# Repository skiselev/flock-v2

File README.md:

# Flock - Version 2.0
Floppy Disk Controller and Real Time Clock for RCBus systems

## Table of Content
* [Overview](#overview)
  * [Specifications](#specifications)
* [Assembly Instructions](#assembly-instructions)
* [Hardware Documentation](#hardware-documentation)
  * [Schematic and PCB Layout](#schematic-and-pcb-layout)
  * [Input/Output Ports](#inputoutput-ports)
  * [Connectors](#connectors)
  * [Bill of Materials](#bill-of-materials)
* [Release Notes](#release-notes)
  * [Changes](#changes)
  * [Known Issues](#known-issues)
* [Red Tape](#red-tape)
  * [Licensing](#licensing)
  * [Trademarks](#trademarks)

## Overview
Flock is an RCBus floppy disk controller (FDC) and real time clock (RTC) module. It designed to work with RomWBW firmware, supporting CP/M, ZSDOS, and various applications under these OSes.

### Specifications
* Floppy Disk Controller: Western Digital* WD37C65 or compatible
  * NEC uPD765 compatible with an integrated data separator, floppy interface drivers, and buffers
* Supported floppy disk formats:
  * 3.5", 720 KB
  * 3.5", 1.44 MB
  * 5.25", 360 KB diskettes in 360 MB drive
  * 5.25", 1.2 MB
  * 5.25", 360 KB diskettes in 1.2 MB drive (not supported by RomWBW, requires Y3, C10, and C11 to be installed)
* Supports two floppy drives, using IBM PC-like cable with twisted Disk Select / Motor Enable wires between two drives
* Real Time Clock: Maxim Integrated DS1302
* Bus: RCBus, RC2014* compatible

## Assembly Instructions

Please refer to [Assembly Instructions](Assembly_Instructions.md) document

## Hardware Documentation

### Schematic and PCB Layout

[Schematic - Version 2.0](KiCad/Z80-FDC-V2-Schematic-2.0.pdf)

[PCB Layout - Version 2.0](KiCad/Z80-FDC-V2-Board-2.0.pdf)

### Input/Output Ports

Flock uses the following I/O ports:

#### 0x48 - FDC CCR/DIR

Write: Floppy disk controller control configuration register (CCR)
Read: Floppy disk controller digital input register (DIR)

#### 0x50 - FDC MSR

Read: Floppy disk controller master status register (MSR)

#### 0x51 - FDC Data Register

Read/Write: Data from/to floppy disk controller

#### 0x58 - FDC DOR / TC

Write: Floppy disk controller digital output register (DOR)
Read: Toggle floppy disk controller transfer complete (TC) line

#### 0x0C or 0xC0 - RTC

Read/Write: Access real time clock (RTC)
The RTC address is configured using JP1 jumper

### Jumpers and Connectors

#### JP1 - RTC I/O address select

Position       | Description
-------------- | -----------------
open (default) | RTC address: 0xC0
closed         | RTC address: 0x0C

* Use 0xC0 address for Z80-based systems and 0x0C address for Z180-based systems

#### JP2 - Enable RTC

Position       | Description
-------------- | -----------------
1-2 (default)  | RTC enabled
2-3            | RTC disabled

* JP2 is a solder jumper, located on the back of the board
* By default positions 1-2 are connected with a PCB trace
* If the system already has an RTC or the RTC functionality is not needed:
  * Cut the PCB trace between positions 1-2
  * Connect positions 2-3 with a solder bridge

#### JP3 - Enable 300 Kbps transfer rate support

Position       | Description
-------------- | -----------------
1-2 (default)  | 300 Kbps disabled
2-3            | 300 Kbps enabled

* JP3 is a solder jumper, located on the back of the board
* By default positions 1-2 are connected with a PCB trace
* If 300 Kbps is desired:
  * Cut the PCB trace between positions 1-2
  * Connect positions 2-3 with a solder bridge
  * Install Y3, C10, and C11

#### J1 - Floppy
Connect to floppy drive interface connector.

Pin   | Signal Name | Description   | Pin   | Signal Name | Description
----- | ----------- | --------------| ----- | ----------- | -----------
J1-1  | GND         | Ground        | J1-2  | /DENSEL     | Density Select: 1 = Low density; 0 = High density
J1-3  | N/C         | Not connected | J1-4  | N/C         | Not connected
J1-5  | GND         | Ground        | J1-6  | N/C         | Not connected
J1-7  | GND         | Ground        | J1-8  | /INDEX      | Index hole: 0 = At the index hole
J1-9  | N/C         | Not connected | J1-10 | /MEA        | Motor Enable - Drive A
J1-11 | GND         | Ground        | J1-12 | /DSB        | Drive Select - Drive B
J1-13 | GND         | Ground        | J1-14 | /DSA        | Drive Select - Drive A
J1-15 | GND         | Ground        | J1-16 | /MEB        | Motor Enable - Drive B
J1-17 | N/C         | Not connected | J1-18 | /DIR        | Direction Select
J1-19 | GND         | Ground        | J1-20 | /STEP       | Head Step
J1-21 | GND         | Ground        | J1-22 | /WDATA      | Write Data
J1-23 | GND         | Ground        | J1-24 | /WE         | Write Enable: 0 = Write Enabled
J1-25 | GND         | Ground        | J1-26 | /TRK0       | Track 00: 0 = At the track 0
J1-27 | N/C         | Not connected | J1-28 | /WP         | Write Protect: 0 = Floppy disk is write protected
J1-29 | GND         | Ground        | J1-30 | /RDATA      | Read Data 
J1-31 | GND         | Ground        | J1-32 | /HDSEL      | Head Select / Side Select: 1 = Side 0; 0 = Side 1
J1-33 | N/C         | Not connected | J1-34 | /DC         | Disk changed: 1 = Disk changed; 0 = Ready

#### J2 - Floppy 5V
Connect to floppy 5V power supply connector.

**Important: J2 is an unfused 5V power supply for a single 3.5" floppy disk drive. Avoid overloading and short-circuiting**

Pin | Signal Name | Description
--- | ----------- | -----------
1   | 5V          | Positive terminal - +5V
2   | GND         | Negative terminal - ground

#### J3 - RCBus
Pin   | Signal Name | Description                             | Pin   | Signal Name | Description
----- | ----------- | --------------------------------------- | ----- | ----------- | -----------
J3-1  | A15         | Address A15; Input; Not connected       | J3-41 | p41         | Reserved; Not connected
J3-2  | A14         | Address A14; Input; Not connected       | J3-42 | /BAI        | Bus Acknowledge In; Not connected
J3-3  | A13         | Address A13; Input; Not connected       | J3-43 | /BAO        | Bus Acknowledge Out; Not connected
J3-4  | A12         | Address A12; Input; Not connected       | J3-44 | p44         | Reserved; Not connected
J3-5  | A11         | Address A11; Input; Not connected       | J3-45 | p45         | Reserved; Not connected
J3-6  | A10         | Address A10; Input; Not connected       | J3-46 | p46         | Reserved; Not connected
J3-7  | A9          | Address A9; Input; Not connected        | J3-47 | p47         | Reserved; Not connected
J3-8  | A8          | Address A8; Input; Not connected        | J3-48 | p48         | Reserved; Not connected
J3-9  | A7          | Address A7; Input                       | J3-49 | A23         | Address A23; Input; Not connected
J3-10 | A6          | Address A6; Input                       | J3-50 | A22         | Address A22; Input; Not connected
J3-11 | A5          | Address A5; Input                       | J3-51 | A21         | Address A21; Input; Not connected
J3-12 | A4          | Address A4; Input                       | J3-52 | A20         | Address A20; Input; Not connected
J3-13 | A3          | Address A3; Input                       | J3-53 | A19         | Address A19; Input; Not connected
J3-14 | A2          | Address A2; Input                       | J3-54 | A18         | Address A18; Input; Not connected
J3-15 | A1          | Address A1; Input                       | J3-55 | A17         | Address A17; Input; Not connected
J3-16 | A0          | Address A0; Input                       | J3-56 | A16         | Address A16; Input; Not connected
J3-17 | GND         | Ground                                  | J3-57 | GND         | Ground
J3-18 | VCC         | Power Supply - +5V                      | J3-58 | VCC         | Power Supply - +5V
J3-19 | /M1         | Machine Cycle One; Input                | J3-59 | /RFSH       | DRAM refresh; Input; Not connected
J3-20 | /RESET      | Reset; Input                            | J3-60 | PAGE        | Page ROM/RAM input; Not connected
J3-21 | CLK1        | CPU Clock; Input; Not connected         | J3-61 | CLK2        | UART Clock (programmable); Input; Not connected
J3-22 | /INT        | Interrupt; Output; Not connected        | J3-62 | /BUSACK     | DMA Bus Acknowledge; Input; Not connected
J3-23 | /MREQ       | Memory Request; Input; Not connected    | J3-63 | /HALT       | Halt; Input; Not connected
J3-24 | /WR         | Write Request; Input                    | J3-64 | /BUSREQ     | DMA Bus Request; Output; Not connected
J3-25 | /RD         | Read Request; Input                     | J3-65 | /WAIT       | Wait; Output; Not connected
J3-26 | /IORQ       | Input/Output Request; Input             | J3-66 | /NMI        | Non-maskable Interrupt; Output; Not connected
J3-27 | D0          | Data D0; Input/Output                   | J3-67 | D8          | Data D8; Input/Output; Not connected
J3-28 | D1          | Data D1; Input/Output                   | J3-68 | D9          | Data D9; Input/Output; Not connected
J3-29 | D2          | Data D2; Input/Output                   | J3-69 | D10         | Data D10; Input/Output; Not connected
J3-30 | D3          | Data D3; Input/Output                   | J3-70 | D11         | Data D11; Input/Output; Not connected
J3-31 | D4          | Data D4; Input/Output                   | J3-71 | D12         | Data D12; Input/Output; Not connected
J3-32 | D5          | Data D5; Input/Output                   | J3-72 | D13         | Data D13; Input/Output; Not connected
J3-33 | D6          | Data D6; Input/Output                   | J3-73 | D14         | Data D14; Input/Output; Not connected
J3-34 | D7          | Data D7; Input/Output                   | J3-74 | D15         | Data D15; Input/Output; Not connected
J3-35 | TX          | Channel 1, Transmit Data; Not Connected | J3-75 | TX2         | Channel 2, Transmit Data; Not Connected
J3-36 | RX          | Channel 1, Receive Data; Not Connected  | J3-76 | RX2         | Channel 2, Receive Data; Not Connected
J3-37 | /IRQ1       | Interrupt Request 1; Not connected      | J3-77 | /IRQ2       | Interrupt Request 2; Not connected
J3-38 | IEI         | Interrupt Enable In; Not connected      | J3-78 | p78         | Reserved; Not connected
J3-39 | IEO         | Interrupt Enable Out; Not connected     | J3-79 | p79         | Reserved; Not connected
J3-40 | USER4       | User Pin 4; Not connected               | J3-80 | USER8       | User Pin 8; Not connected

### Bill of Materials

#### Version 2.0

[Flock V2 project on Mouser.com](https://www.mouser.com/ProjectManager/ProjectDetail.aspx?AccessID=57797d9ea4) - View and order all components except of the FDC and the PCB.

[Flock project on OSH Park](https://oshpark.com/shared_projects/vQHiVNa8) - View and order the PCB.

Flock project on Tindie: [Complete kit](https://www.tindie.com/products/weird/flock-v2-rcbus-module-kit/); [Flock PCB, FDC, RTC, and SPLD](https://www.tindie.com/products/weird/flock-v2-rcbus-module-pcb-fdc-rtc-and-spld/).

Component type     | Reference | Description                                 | Quantity | Possible sources and notes 
------------------ | --------- | ------------------------------------------- | -------- | --------------------------
PCB                |           | Flock PCB - Version 2.0                     | 1        | Buy from my Tindie store: [Complete kit](https://www.tindie.com/products/weird/flock-v2-rcbus-module-kit/); [Flock PCB, FDC, RTC, and SPLD](https://www.tindie.com/products/weird/flock-v2-rcbus-module-pcb-fdc-rtc-and-spld/)., or order from a PCB manufacturer of your choice using provided Gerber or KiCad files
Integrated Circuit | U1        | WD37C65BJM - FDC, CMOS, 44 pin PLCC         | 1        | eBay. Alternative: ST AIC37C65CL
Integrated Circuit | U2        | DS1302+ - RTC, 8 pin DIP                    | 1        | Mouser [700-DS1302](https://www.mouser.com/ProductDetail/700-DS1302)
Integrated Circuit | U3        | ATF16V8B-15PU - Simple Programmable Logic Device, 20 pin DIP | 1 | Mouser [556-AF16V8B15PU](https://www.mouser.com/ProductDetail/556-AF16V8B15PU)
Integrated Circuit | U4        | 74AHCT174 - Hex D-type flip-flop with reset, 16 pin DIP | 1 | Mouser [595-SN74AHCT174N](https://www.mouser.com/ProductDetail/595-SN74AHCT174N)
Integrated Circuit | U5        | 74HCT125 - Quadruple bus buffer gates with 3-state outputs, 14 pin DIP | 1 | Mouser [595-SN74HCT125NE4](https://www.mouser.com/ProductDetail/595-SN74HCT125NE4)
Quartz Crystal     | Y1        | 16 MHz, series                              | 1        | Mouser [774-ATS160-E](https://www.mouser.com/ProductDetail/774-ATS160-E)
Quartz Crystal     | Y2        | 32768 Hz, 6 pF                              | 1        | Mouser [815-AB26T32768KHZ6B](https://www.mouser.com/ProductDetail/815-AB26T32768KHZ6B)
Quartz Crystal     | Y3        | 9.6 MHz, series                             | 1        | Optional; Install for 300 Kbps transfer rate support
Connector          | J1        | 2x17 pin header, shrouded, 2.54 mm pitch, right angle | 1 | Mouser [517-30334-5002](https://www.mouser.com/ProductDetail/517-30334-5002)
Connector          | J2        | 2 pin header with friction lock, right angle | 1       | Mouser [571-2-644488-2](https://www.mouser.com/ProductDetail/571-2-644488-2)
Pin Header         | J3        | 2x40 pin header, 2.54 mm pitch, right angle | 1        | Mouser [517-5121TG](https://www.mouser.com/ProductDetail/517-5121TG)
Pin Header         | JP1       | 2 pin header, 2.54 mm pitch                 | 1        | Mouser [649-68002-102HLF](https://www.mouser.com/ProductDetail/649-68002-102HLF)
Jumper             | JP1       | Shunt, 2 pin 2.54 mm pitch                  | 1        | Mouser [806-SX1100-B](https://www.mouser.com/ProductDetail/806-SX1100-B)
Battery Holder     | BT1       | CR2032 battery holder                       | 1        | Mouser [122-2620-GR](https://www.mouser.com/ProductDetail/122-2620-GR) or [122-2420-GR](https://www.mouser.com/ProductDetail/122-2420-GR). Install either BT1 or C7
Battery            | BT1       | CR2032 battery                              | 1        | Mouser [81-CR2032](https://www.mouser.com/ProductDetail/81-CR2032), [658-CR2032](https://www.mouser.com/ProductDetail/658-CR2032), or [614-CR2032-200](https://www.mouser.com/ProductDetail/614-CR2032-200). Install either BT1 or C7
Capacitor          | C1 - C5   | 0.1 uF, 50V, MLCC, 5 mm pitch               | 5        | Mouser [810-FG28X7R1H104KNT6](https://www.mouser.com/ProductDetail/810-FG28X7R1H104KNT6)
Capacitor          | C6        | 10 uF, 47V, Organic Polymer, 6.3 mm diameter, 2.5 mm pitch | 1 | Mouser [80-A759EA106M1JAAE60](https://www.mouser.com/ProductDetail/80-A759EA106M1JAAE60). Note: PCB silkscreen specifies 47uF capacitor. 10uF - 47uF capacitor with voltage rating 10V or more can be used
Capacitor          | C7        | 0.22 F, 5.5V, Supercapacitor, 13.5 mm diameter, 5 mm pitch | 1 | Mouser [555-DBN-5R5D334T](https://www.mouser.com/ProductDetail/555-DBN-5R5D334T). Install either BT1 or C7
Capacitor          | C8        | 47 pF, 50V, MLCC, 5 mm pitch                | 1        | Mouser [810-FG28C0G2A470JNT0](https://www.mouser.com/ProductDetail/810-FG28C0G2A470JNT0)
Capacitor          | C9        | 15 pF, 50V, MLCC, 5 mm pitch                | 1        | Mouser [810-FG28C0G2A150JNT0](https://www.mouser.com/ProductDetail/810-FG28C0G2A150JNT0)
Capacitor          | C10       | 68 pF, 50V, MLCC, 5 mm pitch                | 1        | Optional; Install for 300 Kbps transfer rate support
Capacitor          | C11       | 56 pF, 50V, MLCC, 5 mm pitch                | 1        | Optional; Install for 300 Kbps transfer rate support
Resistor Array     | RN1       | 1 kohm, bussed, 6 pin SIP                   | 1        | Mouser [652-4606X-1LF-1K](https://www.mouser.com/ProductDetail/652-4606X-1LF-1K)
Resistor           | R1 - R3   | 10 kohm, 0.25 W, 1% tolerance, axial        | 3        | Mouser [603-MFR-25FRF5210K](https://www.mouser.com/ProductDetail/603-MFR-25FRF5210K)
IC Socket          | U1        | 44 pin PLCC, through hole                   | 1        | Mouser [649-54020-44030LF](https://www.mouser.com/ProductDetail/649-54020-44030LF), [517-8444-11B1-RK-TP](https://www.mouser.com/ProductDetail/517-8444-11B1-RK-TP)
IC Socket          | U2        | 8 pin DIP                                   | 1        | Mouser [649-DILB8P223TLF](https://www.mouser.com/ProductDetail/649-DILB8P223TLF)
IC Socket          | U3        | 20 pin DIP                                  | 1        | Mouser [649-DILB20P-223TLF](https://www.mouser.com/ProductDetail/649-DILB20P-223TLF)
IC Socket          | U4        | 16 pin DIP                                  | 1        | Mouser [649-DILB16P-223TLF](https://www.mouser.com/ProductDetail/649-DILB16P-223TLF)
IC Socket          | U5        | 14 pin DIP                                  | 1        | Mouser [649-DILB14P-223TLF](https://www.mouser.com/ProductDetail/649-DILB14P-223TLF)
Connector          | J2        | 2 pin connector                             | 1        | Mouser [571-3-643813-2](https://www.mouser.com/ProductDetail/571-3-643813-2)
Connector          | J2        | Floppy disk power connector housing         | 1        | Mouser [571-1718224](https://www.mouser.com/ProductDetail/571-1718224)
Connector          | J2        | Floppy disk power connector contacts        | 2        | Mouser [571-170262-2-LP](https://www.mouser.com/ProductDetail/571-170262-2-LP), [571-1702622-CT](https://www.mouser.com/ProductDetail/571-1702622-CT) (strip of 100 contacts)

## Release Notes

### Changes

* Version 2.0
  * Update form factor from RC2014* compatible to RCBus
  * Add an option to use CR2032 battery instead of a super capacitor for the RTC
  * Use right angle connector for the floppy interface
  * Use ATF16V8B SPLD for address decode
  * Add JP1 jumper for selecting RTC I/O address. Either 0xC0 or 0x0C can be used
  * Add JP2 jumper for disabling the RTC.
  * Add an option to support 300 Kbps transfer speed
  * Add a header for GPIO signals
* Version 1.0
  * Initial version

### Known Issues

* Version 1.0
  * No known issues

### Wishlist
* None so far

## Red Tape

### Licensing

Flock is an open source hardware project certified by [Open Source Hardware Association](https://www.oshwa.org/), certification UID is [US002115](https://certification.oshwa.org/us002115.html). The hardware design itself, including schematic and PCB layout design files are licensed under the strongly-reciprocal variant of [CERN Open Hardware Licence version 2](license-cern_ohl_s_v2.txt). The CPLD VHDL code is licensed under [GNU General Public License v3](license-gpl-3.0.txt). Documentation, including this file, is licensed under the [Creative Commons Attribution-ShareAlike 4.0 International License](license-cc-by-sa-4.0.txt).

### Trademarks

* "RC2014" is a registered trademark of RFC2795 Ltd.
* Other names and brands may be claimed as the property of others.

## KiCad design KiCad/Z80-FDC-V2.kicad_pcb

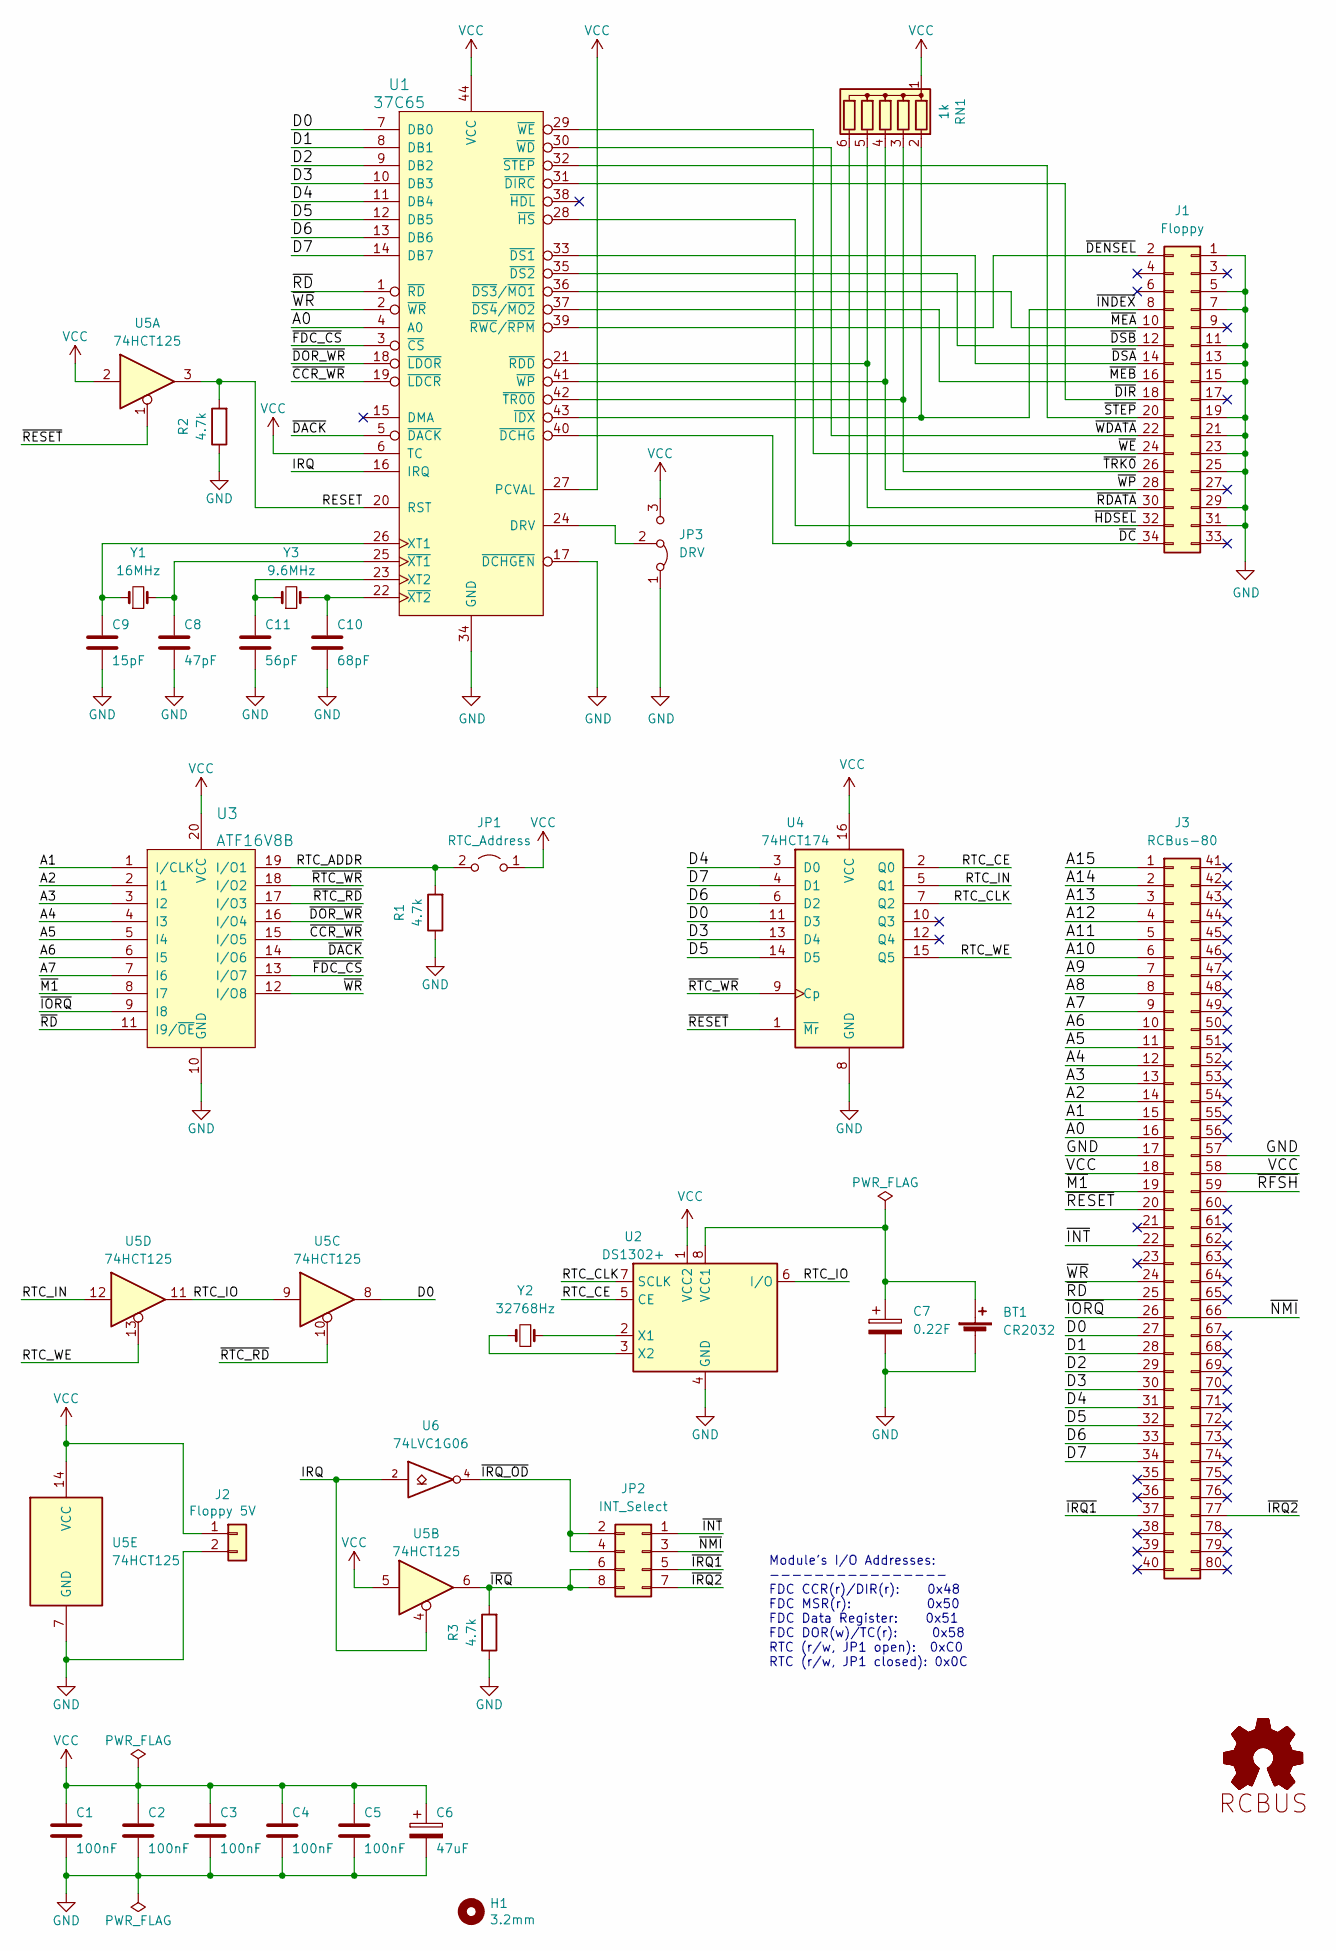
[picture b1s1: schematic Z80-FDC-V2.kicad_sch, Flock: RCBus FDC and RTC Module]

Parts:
BT1: CR2032; Battery_Holder_CR2032_Universal
C1, C2, C3, C4, C5: 100nF; Cap_Cer_508
C6: 47uF; Cap_Elec_Radial_6.3mm
C7: 0.22F; Cap_Super_Radial_13.5mm
C8: 47pF; Cap_Cer_508
C9: 15pF; Cap_Cer_508
C10: 68pF; Cap_Cer_508
C11: 56pF; Cap_Cer_508
H1: 3.2mm; MountingHole_3.2mm_M3_DIN965
J1: Floppy; Conn_Pin_Header_17x2_2.54mm_Shrouded_RA
J2: Floppy 5V; Conn_TE_2-644488-2_2P_2.54mm
J3: RCBus-80; Conn_Pin_Header_40x2_2.54mm_Right_Angle_RCBus80
JP1: RTC_Address; Conn_Pin_Header_2x1_2.54mm_NoKey
JP2: INT_Select; Conn_Pin_Header_4x2_2.54mm
JP3: DRV; Conn_Pin_Header_3x1_2.54mm
LOGO1, LOGO2: Logo_Open_Hardware_Small; OSHW-Logo_5.7x6mm_SilkScreen
LOGO3: RCBUS_Logo
R1, R2, R3: 4.7k; Res_762
RN1: 1k; Conn_SIL6
U1: 37C65; IC_PLCC44_TH
U2: DS1302+; IC_DIP8_300
U3: ATF16V8B; IC_DIP20_300
U4: 74HCT174; IC_DIP16_300
U5: 74HCT125; IC_DIP14_300
U6: 74LVC1G06; SOT-23-5_HandSoldering
Y1: 16MHz; Crystal_HC-49U_Vert
Y2: 32768Hz; Crystal_32K_Horiz
Y3: 9.6MHz; Crystal_HC-49U_Vert

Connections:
/A0: J3.16, U1.4 (A0)
/A1: J3.15, U3.1 (I/CLK)
/A2: J3.14, U3.2 (I1)
/A3: J3.13, U3.3 (I2)
/A4: J3.12, U3.4 (I3)
/A5: J3.11, U3.5 (I4)
/A6: J3.10, U3.6 (I5)
/A7: J3.9, U3.7 (I6)
/A8: J3.8
/A9: J3.7
/A10: J3.6
/A11: J3.5
/A12: J3.4
/A13: J3.3
/A14: J3.2
/A15: J3.1
/D0: J3.27, U1.7 (DB0), U4.11 (D3), U5.8
/D1: J3.28, U1.8 (DB1)
/D2: J3.29, U1.9 (DB2)
/D3: J3.30, U1.10 (DB3), U4.13 (D4)
/D4: J3.31, U1.11 (DB4), U4.3 (D0)
/D5: J3.32, U1.12 (DB5), U4.14 (D5)
/D6: J3.33, U1.13 (DB6), U4.6 (D2)
/D7: J3.34, U1.14 (DB7), U4.4 (D1)
/IRQ: U1.16 (IRQ), U5.4, U6.2
/RESET: R2.2, U1.20 (RST), U5.3
/RTC_ADDR: JP1.2 (B), R1.2, U3.19 (I/O1)
/RTC_CE: U2.5 (CE), U4.2 (Q0)
/RTC_CLK: U2.7 (SCLK), U4.7 (Q2)
/RTC_IN: U4.5 (Q1), U5.12
/RTC_IO: U2.6 (I/O), U5.9, U5.11
/RTC_WE: U4.15 (Q5), U5.13
/~CCR_WR: U1.19 (~LDCR), U3.15 (I/O5)
/~DACK: U1.5 (~DACK), U3.14 (I/O6)
/~DC: J1.34, RN1.6 (R5), U1.40 (~DCHG)
/~DENSEL: J1.2, U1.39 (~RWC/~RPM)
/~DIR: J1.18, U1.31 (~DIRC)
/~DOR_WR: U1.18 (~LDOR), U3.16 (I/O4)
/~DSA: J1.14, U1.33 (~DS1)
/~DSB: J1.12, U1.35 (~DS2)
/~FDC_CS: U1.3 (~CS), U3.13 (I/O7)
/~HDSEL: J1.32, U1.28 (~HS)
/~INDEX: J1.8, RN1.2 (R1), U1.43 (~IDX)
/~INT: J3.22, JP2.1
/~IORQ: J3.26, U3.9 (I8)
/~IRQ1: J3.37, JP2.5
/~IRQ2: J3.77, JP2.7
/~IRQ_OD: JP2.2, JP2.4, U6.4
/~IRQ: JP2.6, JP2.8, R3.2, U5.6
/~M1: J3.19, U3.8 (I7)
/~MEA: J1.10, U1.36 (~DS3/~MO1)
/~MEB: J1.16, U1.37 (~DS4/~MO2)
/~NMI: J3.66, JP2.3
/~RDATA: J1.30, RN1.5 (R4), U1.21 (~RDD)
/~RD: J3.25, U1.1 (~RD), U3.11 (I9/~OE)
/~RESET: J3.20, U4.1 (~Mr), U5.1
/~RFSH: J3.59
/~RTC_RD: U3.17 (I/O3), U5.10
/~RTC_WR: U3.18 (I/O2), U4.9 (Cp)
/~STEP: J1.20, U1.32 (~STEP)
/~TRK0: J1.26, RN1.3 (R2), U1.42 (~TR00)
/~WDATA: J1.22, U1.30 (~WD)
/~WE: J1.24, U1.29 (~WE)
/~WP: J1.28, RN1.4 (R3), U1.41 (~WP)
/~WR: J3.24, U1.2 (~WR), U3.12 (I/O8)
GND: BT1.2 (-), C1.2, C2.2, C3.1, C4.2, C5.2, C6.2, C7.2, C8.2, C9.2, C10.2, C11.2, J1.1, J1.5, J1.7, J1.11, J1.13, J1.15, J1.19, J1.21, J1.23, J1.25, J1.29, J1.31, J2.2, J3.17, J3.57, JP3.1 (A), R1.1, R2.1, R3.1, U1.17 (~DCHGEN), U1.34 (GND), U2.4 (GND), U3.10 (GND), U4.8 (GND), U5.7 (GND), U6.3 (GND)
unnamed: BT1.1 (+), C7.1, U2.8 (VCC1)
unnamed: C10.1, U1.22 (~XT2), Y3.2
unnamed: C11.1, U1.23 (XT2), Y3.1
unnamed: JP3.2 (C), U1.24 (DRV)
unnamed: C8.1, U1.25 (~XT1), Y1.2
unnamed: C9.1, U1.26 (XT1), Y1.1
unnamed: U2.2 (X1), Y2.1
unnamed: U2.3 (X2), Y2.2
VCC: C1.1, C2.1, C3.2, C4.1, C5.1, C6.1, J2.1, J3.18, J3.58, JP1.1 (A), JP3.3 (B), RN1.1 (common), U1.6 (TC), U1.27 (PCVAL), U1.44 (VCC), U2.1 (VCC2), U3.20 (VCC), U4.16 (VCC), U5.2, U5.5, U5.14 (VCC), U6.5 (VCC)

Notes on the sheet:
Module's I/O Addresses: ---------------- FDC CCR(r)/DIR(r): 0x48 FDC MSR(r): 0x50 FDC Data Register: 0x51 FDC DOR(w)/TC(r): 0x58 RTC (r/w, JP1 open): 0xC0 RTC (r/w, JP1 closed): 0x0C

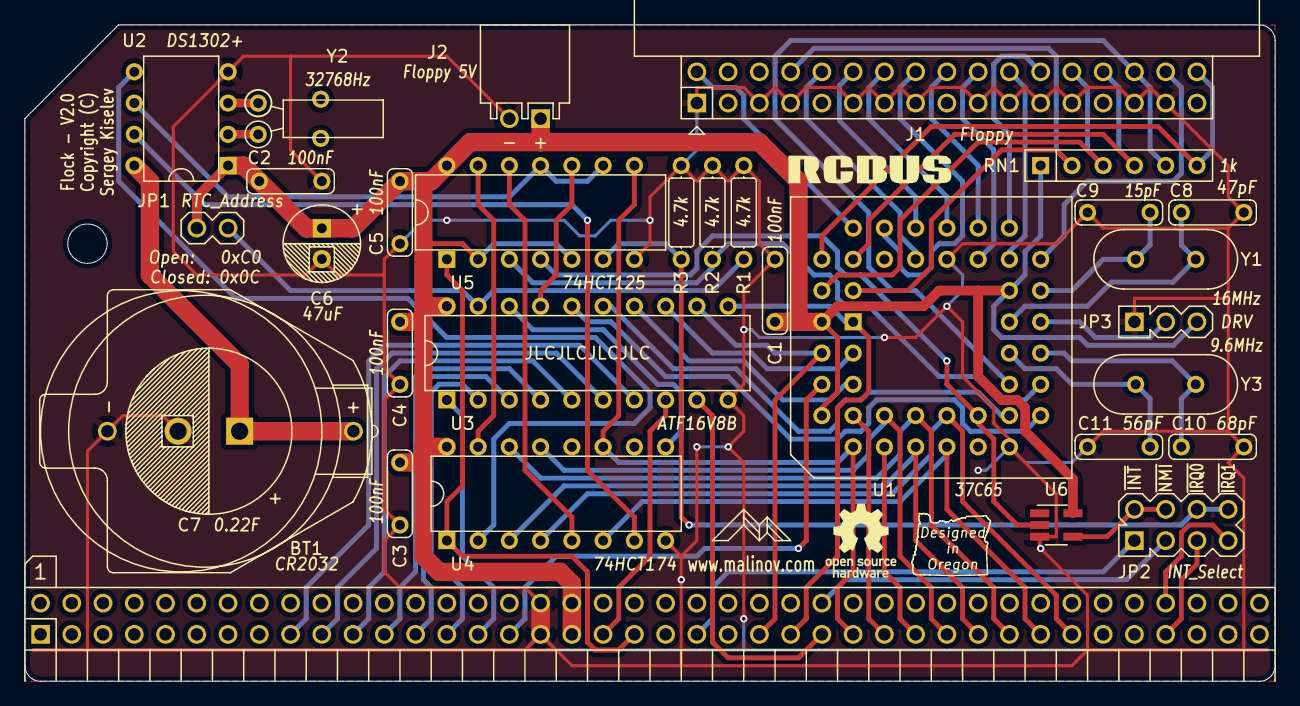
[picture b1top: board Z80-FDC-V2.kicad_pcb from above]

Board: 2 copper layers, 101.6 x 53.3 mm, 35 parts (1 on the bottom side), 66 nets.

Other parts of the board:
LOGO1#2: Logo_Open_Hardware_Small; OSHW-Logo_5.7x6mm_SilkScreen

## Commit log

2023-09-21 Add initial schematic and SPLD code. Copy documentation from Flock V1
2023-10-11 Update BOM and V2 changes
2023-11-09 Add Flock V2 photos and update instructions
2023-11-13 Add jumpers descriptions; update component photos
2023-11-13 Update PCB photo
2023-11-14 Update instructions regarding C6, C7, and BT1
2023-11-14 Update Assembly Instructions
2023-11-14 Clarify polarity marks on C6 and C7
2023-11-14 Remove photos of unused ICs
2024-04-26 README: Update Mouser BoM and OSHPark PCB links
2024-10-16 Fix comment about which capacitor is optional in the assembly instructions.
    Update the comment about which capacitor is optional. That should be C7, the supercapacitor used to keep time, not C6 who is an electrolictic capacitor used for DC filtering.
2025-12-22 README: Fix a typo
2026-01-29 README: Update link to PCB + ICs kit
2026-01-29 README: Fix links to the complete kit

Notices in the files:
KiCad/Z80-FDC-V2.kicad_pcb:
Licensed under CERN-OHL-S: https://cern-ohl.web.cern.ch
Copyright (C) 2022-2023 Sergey Kiselev
Copyright (C)
README.md:
CERN-OHL-2.0-S, GPL-3.0, CC-BY-SA-4.0
